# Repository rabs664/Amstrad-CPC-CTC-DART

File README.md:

# Amstrad CPC CTC DART
Simple Z80 CTC and DART board compatible with the Amstrad CPC and MX4 connector

## Objective
Prototyping board to learn about the Z80 CTC and DART, and how to write Z80 assembly using an Amstrad CPC.

## Background
Part of a number of modular cards using Z80 associated peripherals and the Amstrad CPC.

See also;
[Amstrad CPC 2855 PIO](https://github.com/rabs664/Amstrad-CPC-8255-PIO), [Amstrad CPC Z80 CTC](https://github.com/rabs664/Amstrad-CPC-Z80-CTC) and [Amstrad CPC Z80 DART](https://github.com/rabs664/Amstrad-CPC-Z80-DART)

## Backplane
[CPC Amstrad Expansion Backplane by revaldinho](https://github.com/revaldinho/cpc_ram_expansion/wiki/CPC-Expansion-Backplane)

## IO Addressing
The IO Address can be selected using jumpers, supporting the following base address.

* F8XX
* F9XX
* FAXX
* FBXX

The CTC is then adressed at XXEO and the DART at XXF0.

See [CPC Wiki IO Port Summary](https://www.cpcwiki.eu/index.php/I/O_Port_Summary) for a list of known IO ports used on the Amstrad CPC.

## Testing
The CTC DART board has been built and simple testing has been completed on an Amstrad CPC 6128.

Note also an FTDI Serial Adapter was used to connect to a Tera Term session.

## PCBs
PCBs are available from [Seeed Studio](https://www.seeedstudio.com/Amstrad-CPC-CTC-DART-V1-0-g-1398289).

## Components
This [Digi-Key](https://www.digikey.co.uk/en/mylists/list/81SQJULUKE) List contains all components excluding the Z80 CTC, DART and FTDI Serial Adapter.

## Assembler
[RASM](https://github.com/EdouardBERGE/rasm)

## Resources
[CPCWiki](https://www.cpcwiki.eu/index.php/Main_Page)

Z80 Application by James W Coffron ISBN 0-89588-094-6

## Acknowledgements
[@revaldinho](https://github.com/revaldinho)

Don Prefontaine 

Peter Murray

[@EdouardBERGE](https://github.com/EdouardBERGE)

[@johnwinans](https://github.com/johnwinans)

# Release History
## Version 1.0
* First Release

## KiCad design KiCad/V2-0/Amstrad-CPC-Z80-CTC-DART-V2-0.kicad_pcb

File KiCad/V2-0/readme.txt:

This folder contains files for V2.0.

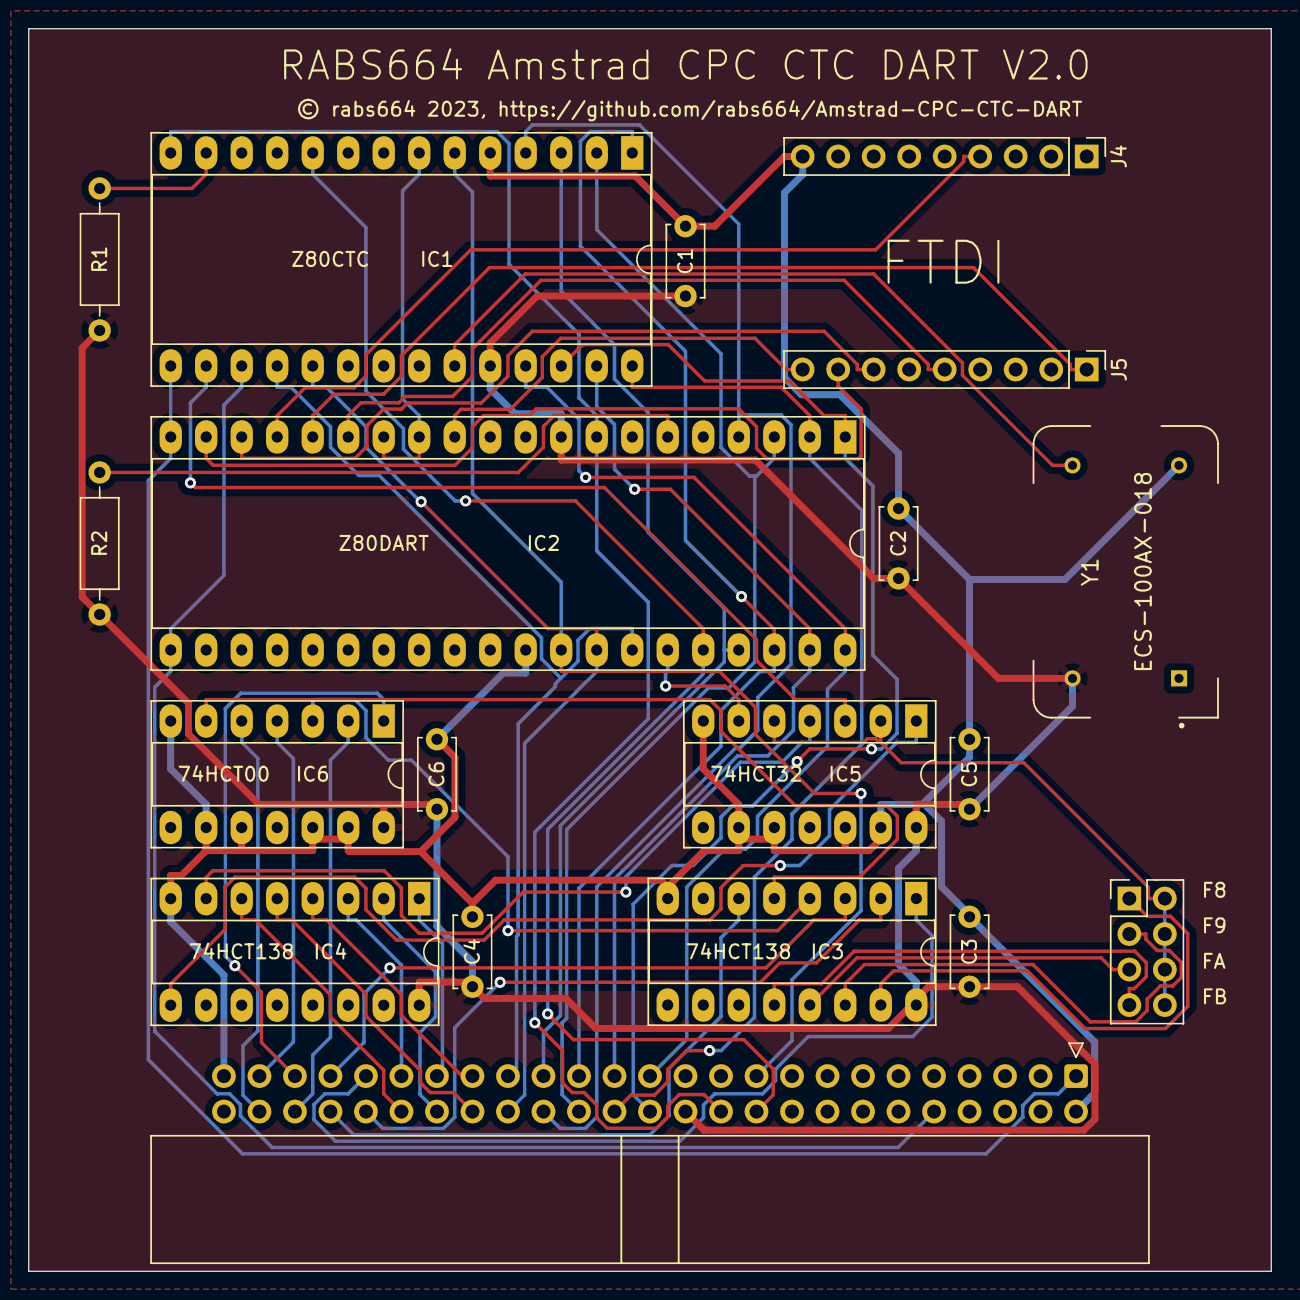
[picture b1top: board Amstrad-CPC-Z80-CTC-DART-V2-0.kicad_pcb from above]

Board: 2 copper layers, 88.9 x 88.9 mm, 19 parts (0 on the bottom side), 52 nets.

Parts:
C1, C2, C3, C4, C5, C6: 100nF; C_Disc_D5.0mm_W2.5mm_P5.00mm
IC1: Z80CTC; DIP-28_W15.24mm_Socket_LongPads
IC2: Z80DART; DIP-40_W15.24mm_Socket_LongPads
IC3, IC4: 74HCT138; DIP-16_W7.62mm_Socket_LongPads
IC5: 74HCT32; DIP-14_W7.62mm_Socket_LongPads
IC6: 74HCT00; DIP-14_W7.62mm_Socket_LongPads
J1: Conn_02x25_Odd_Even; IDC-Header_2x25_P2.54mm_Horizontal
J3: Conn_02x04_Odd_Even; PinHeader_2x04_P2.54mm_Vertical
J4, J5: Conn_01x09_Pin; PinHeader_1x09_P2.54mm_Vertical
R1, R2: 10K; R_Axial_DIN0207_L6.3mm_D2.5mm_P10.16mm_Horizontal
Y1: ECS-100AX-018; OSC_ECS-100AX-018

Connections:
+5V: C1.1, C2.1, C3.1, C4.1, C5.1, C6.1, IC1.24 (VCC), IC2.9 (VCC), IC3.16 (VCC), IC4.16 (VCC), IC5.14 (VCC), IC6.14 (VCC), J1.24, R1.1, R2.1, Y1.14 (+VDC)
/A0: IC1.18 (CS0), IC2.34 (B/~A), J1.33
/A1: IC1.19 (CS1), IC2.33 (C/~D), J1.34
/A2: IC4.4 (E1), J1.35
/A3: IC4.5 (E2), J1.36
/A4: IC4.1 (A0), J1.37
/A5: IC4.2 (A1), J1.38
/A6: IC4.3 (A2), J1.39
/A7: IC4.6 (E3), J1.40
/A8: IC3.1 (A0), J1.41
/A9: IC3.2 (A1), J1.42
/A10: IC3.3 (A2), J1.43
/A11: IC3.6 (E3), J1.44
/A12: IC6.1, J1.45
/A13: IC6.2, J1.46
/A14: IC6.4, J1.47
/A15: IC6.5, J1.48
/BAUD_CLK: IC1.7 (TO0), IC2.13 (RXCA), IC2.14 (TXCA)
/CLK: IC1.15 (CLK), IC2.20 (CLK), J1.1
/CTC_CLK: IC1.23 (TRG0), Y1.8 (OUTPUT)
/CTS: IC2.17 (RTSA), J4.4
/D0: IC1.25 (D0), IC2.40 (D0), J1.25
/D1: IC1.26 (D1), IC2.1 (D1), J1.26
/D2: IC1.27 (D2), IC2.39 (D2), J1.27
/D3: IC1.28 (D3), IC2.2 (D3), J1.28
/D4: IC1.1 (D4), IC2.38 (D4), J1.29
/D5: IC1.2 (D5), IC2.3 (D5), J1.30
/D6: IC1.3 (D6), IC2.37 (D6), J1.31
/D7: IC1.4 (D7), IC2.4 (D7), J1.32
/DCD: IC2.16 (DTRA), J5.1
/DTR: IC2.19 (DCDA), J5.8
/E0: IC4.9 (O6), IC5.1
/F0: IC4.7 (O7), IC5.4
/F8: IC3.15 (O0), J3.1
/F9: IC3.14 (O1), J3.3
/FA: IC3.13 (O2), J3.5
/FB: IC3.12 (O3), J3.7
/RTS: IC2.18 (CTSA), J5.7
/RXD: IC2.15 (TXDA), J5.5
/TXD: IC2.12 (RXDA), J5.9
/~CTC_CE: IC1.16 (CE), IC5.3
/~DART_CE: IC2.35 (CE), IC5.6
/~IORQ: IC1.10 (IORQ), IC2.36 (IORQ), J1.20
/~M1: IC1.14 (M1), IC2.8 (M1), J1.22
/~RD: IC1.6 (RD), IC2.32 (RD), J1.19
/~RESET: IC1.17 (RESET), IC2.21 (RESET), J1.10
GND: C1.2, C2.2, C3.2, C4.2, C5.2, C6.2, IC1.5 (GND), IC2.31 (GND), IC3.8 (GND), IC4.8 (GND), IC5.7 (GND), IC5.9, IC5.10, IC5.12, IC5.13, IC6.7 (GND), IC6.9, IC6.10, IC6.12, IC6.13, J1.2, J1.49, J4.9, Y1.7 (CASE_GND)
unnamed: IC1.13 (IEI), R1.2
unnamed: IC2.6 (IEI), R2.2
unnamed: IC3.4 (E1), IC6.3
unnamed: IC3.5 (E2), IC6.6
unnamed: IC5.2, IC5.5, J3.2, J3.4, J3.6, J3.8

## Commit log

2023-08-25 Create KiCad
2023-08-26 Add files via upload
    Fixed definition of 1 Stop Bit
2023-08-26 Add files via upload
    Forgot to update the header
2023-09-30 Add files via upload
    Archive old files which have now been replaced by simpler files.
2023-09-30 Add files via upload
    Much simplified files.
2023-09-30 Update siotst03.bas
    Added section to receive a char
2023-10-05 Update README.md
    Added acknowledgement for John Winans
2024-08-07 Update readme.txt
    correct error in file extension for basic test program.
2024-08-08 Update siotst03.bas
    Corrected errors in hex data bytes, for some reason had &X and should have been just &.
2024-08-08 Update siotst03.bas
    Corrected hex codes for now RTS/CTS
2024-08-08 Update siotst03.bas
    Revert back to original simpler file without RTS/CTS.
2024-08-09 Update README.md
    Added link to SeeedStudio and remove history for Version 2.0 as the hardware handshaking never worked.
2024-08-09 Delete KiCad/V2-0 directory
    Version 2 hardware handshaking never worked
2024-08-09 Delete Software/Archive directory
    Clean up old files no longer needed
2024-08-09 Add files via upload
    Tera Term Terminal setup showing use of local echo.
2024-08-09 Add files via upload
    Updated siotst03, added siotst07 and dsk file containing both.
2024-08-09 Update readme.txt
    Clean up BASIC software
2025-07-20 Update README.md
    Remove invalid URL links

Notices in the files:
KiCad/V2-0/Amstrad-CPC-Z80-CTC-DART-V2-0.kicad_pcb:
© rabs664 2023, https://github.com/rabs664/Amstrad-CPC-CTC-DART
